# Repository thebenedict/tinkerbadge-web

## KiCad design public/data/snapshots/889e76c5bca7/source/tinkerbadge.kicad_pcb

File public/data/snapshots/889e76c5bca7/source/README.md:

# Tinker Badge hardware

Open **tinkerbadge.kicad_pro** in KiCad 10. The root schematic links to power, processor, display, lighting and peripheral sheets.

- [Specification](docs/spec.md)
- [Current schematic decisions and remaining gates](docs/design/implementation_status.md)
- [Design review, 10 November 2026](docs/design/design_review_2026-11-10.md)
- [Independent review, 11 November 2026](docs/review/design_review_2026-11-11.md) and [the response with the revision 0.3 fixes](docs/review/response_2026-11-11.md)
- [JLCPCB release package and order settings](docs/design/jlcpcb_release.md); order files in `production/jlcpcb/`
- [Reviewed physical-pin assignments](docs/pinouts.md)
- [Verification results](docs/design/verification.md)
- [Enclosure CAD, assembly and fit checks](mechanical/enclosure/README.md); STEP, STL and panel DXF files in `mechanical/enclosure/exports/`
- [Planning BOM and source history](docs/AI_Tinkerers_Badge_Design_BOM_Draft_2026-11-09.md)

The first prototype uses a single nominal 3.3 V rail for logic and the eight RGB LEDs. Regulator tolerance can fall below the LED datasheet minimum, so startup, low-battery, radio and full-white load-step tests are required.

PCB 0.4 retains Qwiic and exposes three GPIOs, serial, I²C and switched 3.3 V on [J503](docs/design/expansion_header.md). The board is fully routed. The A3 front plate provides access to the ten unpopulated holes.

This is a development design. The battery is a two-wire protected pouch cell on a rear JST PH header; charging is enabled at about 270 mA with on-board thermistors. The [review response](docs/review/response_2026-11-11.md) lists what changed in board revision 0.3 and what still needs hardware in hand, starting with a dry-fit of the display flex.

## Repeat the electrical check

Export the complete root schematic netlist using KiCad CLI or the installed Konnect MCP, then run:

```
python3 tools/check_schematic_contracts.py path/to/export.net --output path/to/endpoint-result.json
python3 tools/check_schematic_properties.py path/to/export.net --output path/to/property-result.json
python3 tools/test_contract_checker.py
python3 tools/test_property_checker.py
python3 tools/test_alps_buttons.py
```

The checker compares every physical pin and intentional NC with the separately maintained reviewed block contracts. The separate property checker covers explicitly declared values, part numbers, ratings, population and library associations. Run root ERC and inspect fresh sheet renders as well. Current outputs are in `exports/`, with a six-page PDF and a pinned verification manifest. The one-time capture scripts are not idempotent rebuild commands; rerunning them blindly can duplicate objects. Initial electrical capture used Konnect MCP. The user-approved [outlined-block revision](docs/design/outlined_blocks_review.md) uses bounded native edits, independent visual review and complete before/after exported-netlist comparison.

## Licensing

- Original hardware and mechanical designs: **CERN-OHL-P-2.0**.
- Original software, tools and firmware: **Apache-2.0**.
- Original documentation and artwork: **CC-BY-4.0**.

See [the licensing map](LICENSE.md) and [full license texts](LICENSES/README.md). Generated exports retain their source licenses. [Third-party notices](docs/THIRD_PARTY_NOTICES.md) cover KiCad libraries and manufacturer material.

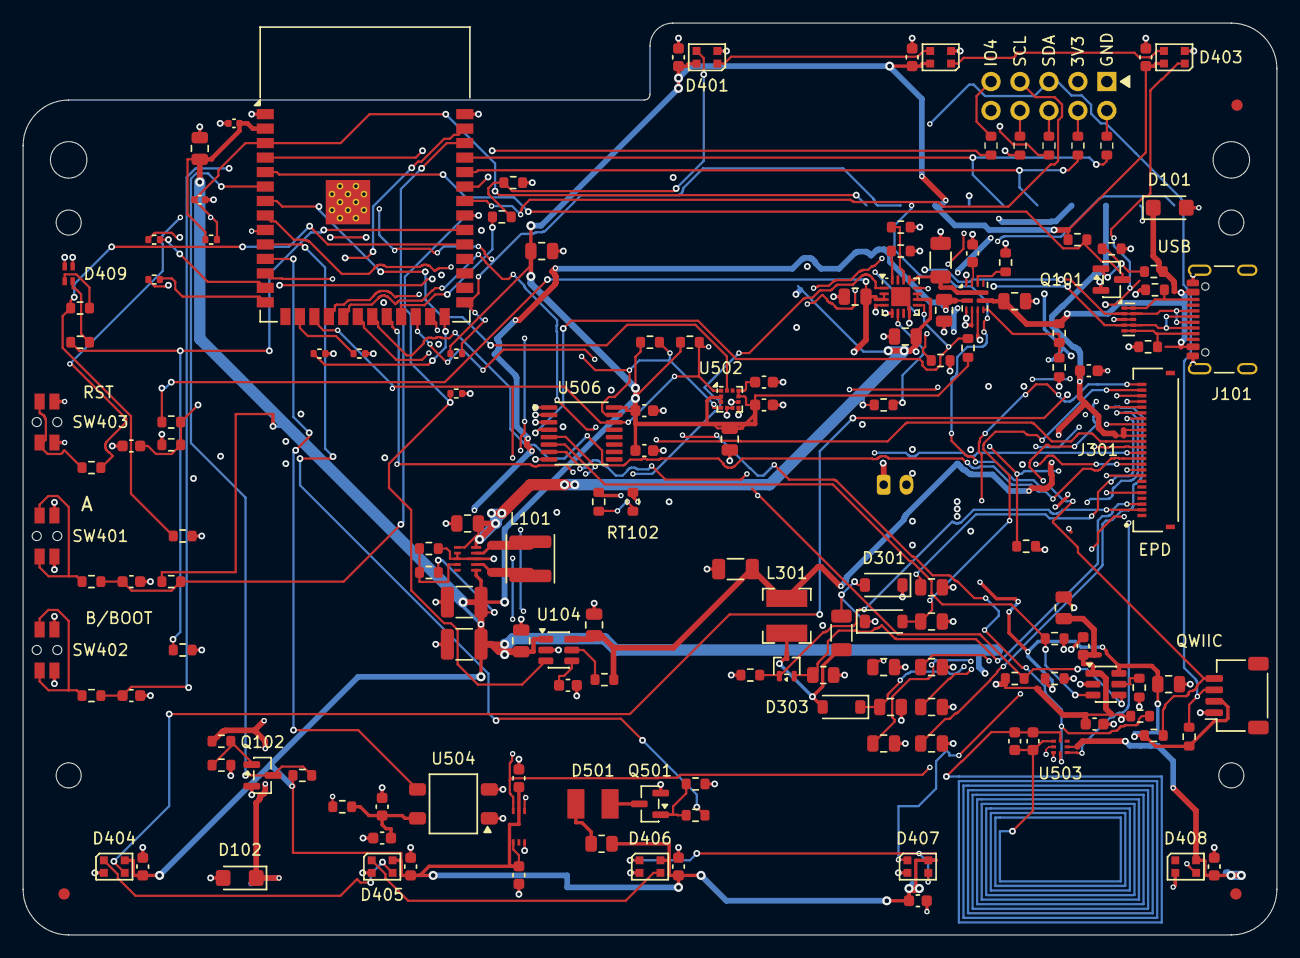
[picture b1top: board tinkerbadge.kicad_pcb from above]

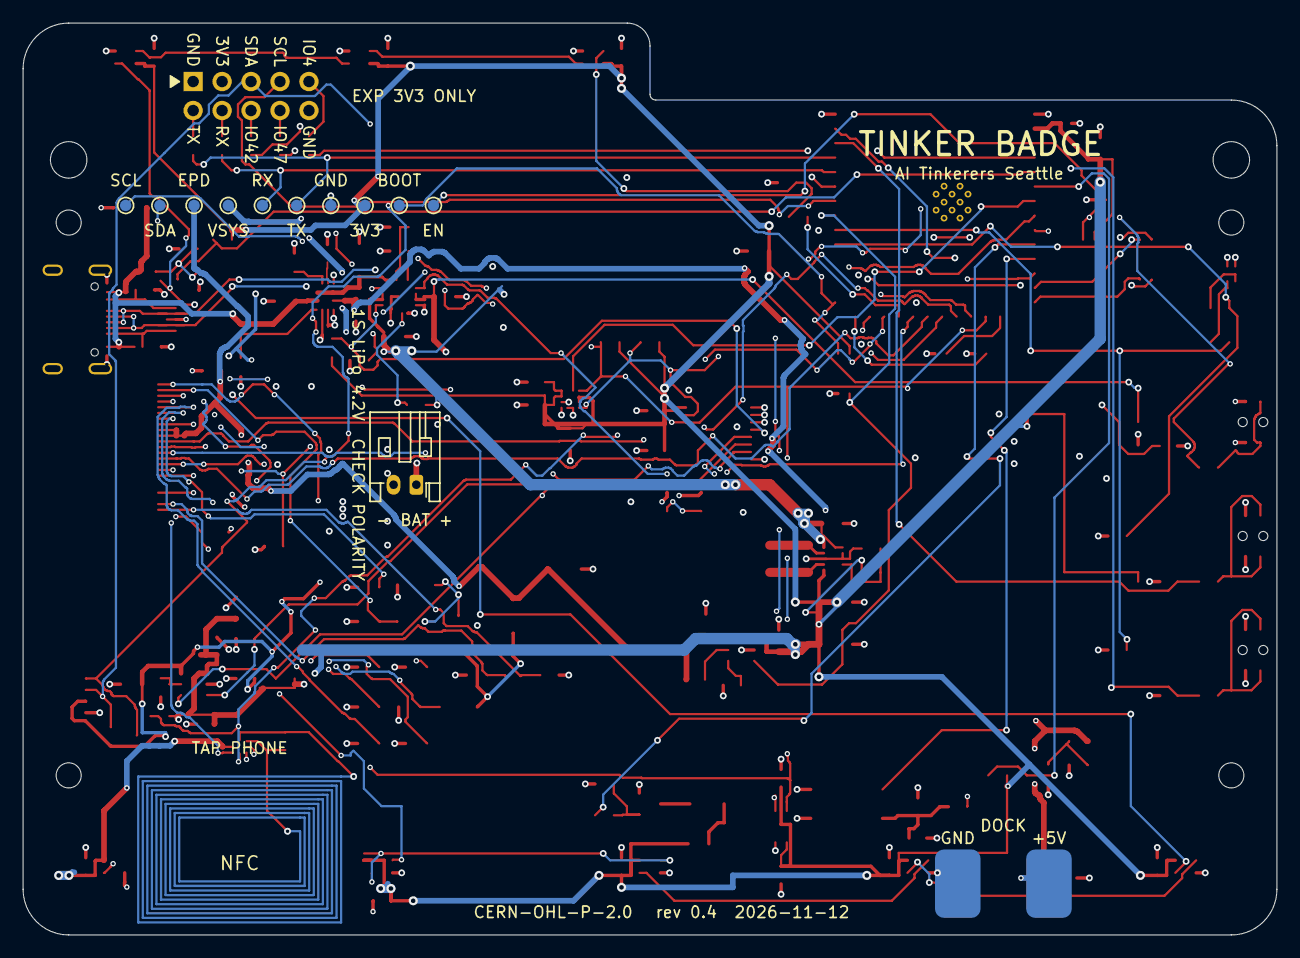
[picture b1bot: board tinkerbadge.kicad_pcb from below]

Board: 4 copper layers, 110.0 x 80.0 mm, 178 parts (14 on the bottom side), 102 nets.

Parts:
AE501: NFC PCB coil; NFC_Coil_Rear_18x13
C101, C102: 1uF 25V X7R; C_0805_2012Metric
C103: 4.7uF 25V X7R; C_1206_3216Metric
C104: 100nF 16V X7R; C_0603_1608Metric
C105, C106, C107: 10uF 10V X7R; C_0805_2012Metric
C108, C109: 22uF 10V X7R; C_1210_3225Metric
C112: 1uF 6.3V X7R; C_0805_2012Metric
C113: 1nF 16V C0G; C_0603_1608Metric
C114: 10uF 6.3V X7R; C_0805_2012Metric
C116: 100nF 6.3V X7R; C_0603_1608Metric
C201: 22uF 10V X5R; C_0805_2012Metric
C202: 100nF 16V X7R; C_0402_1005Metric
C203: 1uF 10V X7R; C_0402_1005Metric
C301, C302: 4.7u / 50V; C_1206_3216Metric
C303, C401, C402, C403, C404, C405, C406, C407, C408, C411, C412, C501, C502, C503, C504, C506, C510, C514: 100n / 10V; C_0603_1608Metric
C304: 1u / 10V; C_0805_2012Metric
C305, C311: 1u / 25V; C_0805_2012Metric
C306, C307, C308, C309, C310: 1u / 50V; C_0805_2012Metric
C409: 22u / 10V; C_0805_2012Metric
C505, C512, C513: 10u / 10V; C_0805_2012Metric
C507: 27p C0G (tune); C_0603_1608Metric
C508: TUNE / DNP; C_0603_1608Metric
C509: 4.7u / 10V; C_0603_1608Metric
C511, C515: 1u / 10V; C_0603_1608Metric
D101, D102: SMF6.0A
D301, D302, D303: MBR0530T1G; D_SOD-123
D401, D402, D403, D404, D405, D406, D407, D408: WS2812C-2020-V6; WS2812C-2020-V6_Reviewed
D409: HSMF-C165
D501: IR67-21C/TR8; IR67-21C_TR8
FID1, FID2, FID3: Fiducial; Fiducial_1mm_Mask2mm
H1, H2, H3, H4: PROVISIONAL; MountingHole_2.2mm_M2
H5, H6: REVIEW ENVELOPE ONLY; Review_Cord_Hole_3p2
J101: USB4105-GF-A; USB4105-GF-A_ProjectShells
J102: LiPo JST-PH; JST_PH_S2B-PH-K_1x02_P2.00mm_Horizontal
J103: Dock 5V pads; Dock_Pads_2x_4x6mm
J301: ED037TC1_FPC; Hirose_FH34SRJ-24S-0.5SH_PanelOrder
J501: SM04B-SRSS-TB(LF)(SN); JST_SH_SM04B_ProjectTabs
J503: 2x05 2.54 mm, not fitted; Expansion_Header_2x05_P2.54mm
L101: 0.47uH; L_Changjiang_FNR4020S
L301: 68uH; L_Bourns-SRN4018
MECH_BATTERY: REVIEW ONLY; Review_Battery_Allowance
MECH_PANEL: REVIEW ENVELOPE ONLY; Review_Panel_Raised_4p5
Q101, Q102, Q501: AO3400A; SOT-23
Q301: Si1308EDL-T1-GE3; SOT-323_SC-70
R101, R102: 5.1k 1%; R_0603_1608Metric
R107: 30k 1%; R_0603_1608Metric
R108, R118: 10k 1%; R_0603_1608Metric
R109: 82k 1%; R_0603_1608Metric
R111, R116, R121, R123, R124, R126: 100k 1%; R_0603_1608Metric
R112: 4.7k 1%; R_0603_1608Metric
R113: 3.3k 1%; R_0603_1608Metric
R114: 47k 1%; R_0603_1608Metric
R117: 56k 1%; R_0603_1608Metric
R119: 1k 1%; R_0603_1608Metric
R122, R125: 470k 1%; R_0603_1608Metric
R127, R128: 1M 1%; R_0603_1608Metric
R201, R202, R203, R204: 10k 1%; R_0402_1005Metric
R205, R206: 22R 1%; R_0402_1005Metric
R207: 100k 1%; R_0402_1005Metric
R301: 0.47 / 0.25W; R_0805_2012Metric
R302, R503: 10k; R_0603_1608Metric
R308, R402, R405, R406, R412, R506, R509, R510, R511: 100k; R_0603_1608Metric
R401, R411, R413, R415, R518, R519, R520, R521, R522: 330; R_0603_1608Metric
R403, R404: 2.2k; R_0603_1608Metric
R501, R502, R512, R513: 4.7k; R_0603_1608Metric
R504: 100; R_0805_2012Metric
R505, R507: 100; R_0603_1608Metric
R508: 200k; R_0603_1608Metric
RT101: 10k NTC B3950 1%; R_0603_1608Metric
RT102: 100k NTC B3950 1%; R_0603_1608Metric
SW401, SW402, SW403: SKSCLBE010
TP101: VSYS; TestPoint_Pad_D1.0mm
TP201: MCU_EN; TestPoint_Pad_D1.0mm
TP202: BOOT / BTN_B; TestPoint_Pad_D1.0mm
TP203: +3V3; TestPoint_Pad_D1.0mm
TP204: GND; TestPoint_Pad_D1.0mm
TP205: UART_TX; TestPoint_Pad_D1.0mm
TP206: UART_RX; TestPoint_Pad_D1.0mm
TP301: +3V3_EPD; TestPoint_Pad_D1.0mm
TP501: I2C_SDA; TestPoint_Pad_D1.0mm
TP502: I2C_SCL; TestPoint_Pad_D1.0mm
U101: TPS2121RUXR; TPS2121RUXR_Reviewed
U102: BQ24074RGTR; BQ24074RGTR_Reviewed
U103: TPS63802DLAR; TPS63802_DLA0010A_Reviewed
U104: TPS22918DBVR; SOT-23-6
U105: TPD4E05U06DQAR; USON-10_2.5x1.0mm_P0.5mm
U201: ESP32-S3-WROOM-1-N16R8; ESP32-S3-WROOM-1
U501: BH1730FVC; BH1730FVC_WSOF6
U502: LIS2DW12TR; LGA-12_2x2mm_P0.5mm
U503: NT3H2111W0FHKH; NT3H2111W0FHKH_XQFN8
U504: IRM-H638T/TR2; IRM-H638T_Reviewed
U505: TPS2553DBVR; SOT-23-6
U506: TCA9534PWR; TSSOP-16_4.4x5mm_P0.65mm

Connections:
+3V3: C108.1, C109.1, C112.1, C201.1, C202.1, C401.1, C402.1, C403.1, C404.1, C405.1, C406.1, C407.1, C408.1, C409.1, C501.1, C502.1, C503.1, C504.1, C505.1, C506.1, C511.1, C512.1, C514.1, C515.1, D401.4, D402.4, D403.4, D404.4, D405.4, D406.4, D407.4, D408.4, R116.1, R117.1, R123.1, R126.1, R201.1, R202.1, R412.1, R501.1, R502.1, R503.1, R504.1, R510.1, TP203.1, U103.6, U104.1, U201.2, U501.1, U501.5, U502.2, U502.3, U502.9, U502.10, U503.6, U505.1, U506.16
+3V3_EPD: C114.1, C301.1, C303.1, J301.15, J301.16, L301.1, R119.1, TP301.1, U104.6
/01 POWER + CHARGING/BATT_NTC: RT101.1, RT102.1, U102.1
/01 POWER + CHARGING/CHARGER_EN1: R111.2, U102.6
/01 POWER + CHARGING/CHARGER_ILIM: R112.1, U102.12
/01 POWER + CHARGING/CHARGER_ISET: R113.1, U102.16
/01 POWER + CHARGING/CHARGER_TMR: R114.1, U102.14
/01 POWER + CHARGING/DOCK_PRESENT_GATE: Q102.1, R124.2, R125.1
/01 POWER + CHARGING/EPD_CT: C113.1, U104.4
/01 POWER + CHARGING/EPD_QOD: R119.2, U104.5
/01 POWER + CHARGING/MUX_ILM: R109.1, U101.10
/01 POWER + CHARGING/MUX_PRIORITY_USB: R107.2, R108.1, U101.6
/01 POWER + CHARGING/MUX_SS: C104.1, U101.11
/01 POWER + CHARGING/PRIMARY_FB: R117.2, R118.1, U103.4
/01 POWER + CHARGING/PRIMARY_L1: L101.1, U103.9
/01 POWER + CHARGING/PRIMARY_L2: L101.2, U103.7
/01 POWER + CHARGING/USB_CC1: J101.A5, R101.1, U105.5, U105.6
/01 POWER + CHARGING/USB_CC2: J101.B5, R102.1, U105.1, U105.10
/01 POWER + CHARGING/USB_PRESENT_GATE: Q101.1, R121.2, R122.1
/01 POWER + CHARGING/VBAT_PROTECTED: C106.1, J102.1, R127.1, U102.2, U102.3
/01 POWER + CHARGING/VEXT_5V: C103.1, U101.1, U101.8, U102.13
/01 POWER + CHARGING/VSYS: C105.1, C107.1, R111.1, TP101.1, U102.10, U102.11, U103.1, U103.10
/02 PROCESSOR + RECOVERY/MCU_EN: C203.1, R201.2, R415.2, TP201.1, U201.3
/02 PROCESSOR + RECOVERY/MCU_EN_SW: R415.1, SW403.1, SW403.2
/02 PROCESSOR + RECOVERY/MCU_USB_DM: R205.2, U201.13
/02 PROCESSOR + RECOVERY/MCU_USB_DP: R206.2, U201.14
/02 PROCESSOR + RECOVERY/STRAP45: R203.1, U201.26
/02 PROCESSOR + RECOVERY/STRAP46: R204.1, U201.16
/03 E-PAPER DISPLAY/EPD_GDR: J301.2, Q301.1, R302.1
/03 E-PAPER DISPLAY/EPD_PUMP: C302.2, D301.2, D302.1
/03 E-PAPER DISPLAY/EPD_RESE: J301.3, Q301.2, R301.1
/03 E-PAPER DISPLAY/EPD_SW: C302.1, D303.2, L301.2, Q301.3
/03 E-PAPER DISPLAY/EPD_VCOM: C310.1, J301.24
/03 E-PAPER DISPLAY/EPD_VDD_1V8: C304.1, J301.18
/03 E-PAPER DISPLAY/EPD_VGH: C307.1, D303.1, J301.21
/03 E-PAPER DISPLAY/EPD_VGL: C309.1, D302.2, J301.23
/03 E-PAPER DISPLAY/EPD_VPP: C305.1, J301.19
/03 E-PAPER DISPLAY/EPD_VSH1: C306.1, J301.20
/03 E-PAPER DISPLAY/EPD_VSH2: C311.1, J301.5
/03 E-PAPER DISPLAY/EPD_VSL: C308.1, J301.22
/04 LIGHTING + BUTTONS/BTN_A_SW_N: R411.1, SW401.1, SW401.2
/04 LIGHTING + BUTTONS/BTN_B_SW_N: R413.1, SW402.1, SW402.2
/04 LIGHTING + BUTTONS/PWR_GREEN_A: D409.1, R403.2
/04 LIGHTING + BUTTONS/PWR_RED_A: D409.2, R404.2
/04 LIGHTING + BUTTONS/RGB_DIN: D401.3, R401.2, R402.1
/04 LIGHTING + BUTTONS/RGB_LINK_1: D401.1, D402.3
/04 LIGHTING + BUTTONS/RGB_LINK_2: D402.1, D403.3
/04 LIGHTING + BUTTONS/RGB_LINK_3: D403.1, D404.3
/04 LIGHTING + BUTTONS/RGB_LINK_4: D404.1, D405.3
/04 LIGHTING + BUTTONS/RGB_LINK_5: D405.1, D406.3
/04 LIGHTING + BUTTONS/RGB_LINK_6: D406.1, D407.3
/04 LIGHTING + BUTTONS/RGB_LINK_7: D407.1, D408.3
/05 SENSORS + EXPANSION/ACC_3V3: C513.1, J501.2, J503.3, R511.1, R512.1, R513.1, U505.6
/05 SENSORS + EXPANSION/ACC_EN: R509.1, U505.3, U506.6
/05 SENSORS + EXPANSION/ACC_FAULT_N: R510.2, U505.4, U506.7
/05 SENSORS + EXPANSION/ACC_ILIM: R508.1, U505.5
/05 SENSORS + EXPANSION/HDR_IO4: J503.9, R522.2
/05 SENSORS + EXPANSION/HDR_IO42: J503.6, R520.2
/05 SENSORS + EXPANSION/HDR_IO47: J503.8, R521.2
/05 SENSORS + EXPANSION/HDR_RX: J503.4, R519.2
/05 SENSORS + EXPANSION/HDR_TX: J503.2, R518.2
/05 SENSORS + EXPANSION/IR_GATE: Q501.1, R505.2, R506.1
/05 SENSORS + EXPANSION/IR_LED_A: D501.1, R504.2
/05 SENSORS + EXPANSION/IR_LED_K: D501.2, Q501.3
/05 SENSORS + EXPANSION/IR_RX_3V3: C509.1, C510.1, R507.2, U504.4
/05 SENSORS + EXPANSION/IR_RX_EN: R507.1, U506.5
/05 SENSORS + EXPANSION/NFC_LA: AE501.1, C507.1, C508.1, U503.1
/05 SENSORS + EXPANSION/NFC_LB: AE501.2, C507.2, C508.2, U503.8
BAT_ADC: C116.1, R127.2, R128.1, U201.39
BTN_A_N: C411.1, R411.2, R412.2, U201.38
BTN_B_N: C412.1, R202.2, R413.2, TP202.1, U201.27
CHARGER_CHG_N: R116.2, U102.9, U506.4
DOCK_5V: C102.1, D102.1, J103.1, R124.1, U101.2
DOCK_PRESENT_N: Q102.3, R126.2, U201.6
EPD_BUSY: J301.9, R308.1, U201.8
EPD_CS_N: J301.12, U201.18
EPD_DC: J301.11, U201.21
EPD_EN: R207.1, U104.3, U201.33
EPD_MOSI: J301.14, U201.19
EPD_RST_N: J301.10, U201.22
EPD_SCK: J301.13, U201.20
EXP_IO4: R522.1, U201.4
EXP_IO42: R520.1, U201.35
EXP_IO47: R521.1, U201.24
EXT_SCL: J501.4, J503.7, R513.2, U201.34
EXT_SDA: J501.3, J503.5, R512.2, U201.9
GND: C101.2, C102.2, C103.2, C104.2, C105.2, C106.2, C107.2, C108.2, C109.2, C112.2, C113.2, C114.2, C116.2, C201.2, C202.2, C203.2, C301.2, C303.2, C304.2, C305.2, C306.2, C307.2, C308.2, C309.2, C310.2, C311.2, C401.2, C402.2, C403.2, C404.2, C405.2, C406.2, C407.2, C408.2, C409.2, C411.2, C412.2, C501.2, C502.2, C503.2, C504.2, C505.2, C506.2, C509.2, C510.2, C511.2, C512.2, C513.2, C514.2, C515.2, D101.2, D102.2, D301.1, D401.2, D402.2, D403.2, D404.2, D405.2, D406.2, D407.2, D408.2, D409.3, D409.4, J101.A1, J101.A12, J101.B1, J101.B12, J101.SH, J102.2, J103.2, J301.8, J301.17, J501.1, J503.1, J503.10, Q101.2, Q102.2, Q501.2, R101.2, R102.2, R108.2, R109.2, R112.2, R113.2, R114.2, R118.2, R122.2, R125.2, R128.2, R203.2, R204.2, R207.2, R301.2, R302.2, R308.2, R402.2, R405.2, R406.2, R506.2, R508.2, R509.2, R511.2, RT101.2, RT102.2, SW401.3, SW401.4, SW402.3, SW402.4, SW403.3, SW403.4, TP204.1, U101.3, U101.4, U101.5, U101.12, U102.4, U102.5, U102.8, U102.17, U103.2, U103.3, U103.8, U104.2, U105.3, U105.8, U201.1, U201.40, U201.41, U501.3, U502.5, U502.6, U502.7, U502.8, U503.2, U504.1, U504.2, U505.2, U506.1, U506.2, U506.3, U506.8
I2C_SCL: R502.2, TP502.1, U201.17, U501.6, U502.1, U503.3, U506.14
I2C_SDA: R501.2, TP501.1, U201.12, U501.4, U502.4, U503.5, U506.15
IR_RX_N: U201.11, U504.3
IR_TX: R505.1, U201.10
MOTION_INT1: U201.7, U502.12
NFC_FD_N: R503.2, U201.25, U503.4
PWR_LED_G: R403.1, R405.1, U201.31
PWR_LED_R: R404.1, R406.1, U201.32
RGB_DATA: R401.1, U201.23
UART_RX: R519.1, TP206.1, U201.36
UART_TX: R518.1, TP205.1, U201.37
USB_DM: J101.A7, J101.B7, R205.1, U105.4, U105.7
USB_DP: J101.A6, J101.B6, R206.1, U105.2, U105.9
USB_PRESENT_N: Q101.3, R123.2, U201.5
USB_VBUS: C101.1, D101.1, J101.A4, J101.A9, J101.B4, J101.B9, R107.1, R121.1, U101.7

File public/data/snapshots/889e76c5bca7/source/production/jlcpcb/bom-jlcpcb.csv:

Comment,Designator,Footprint,LCSC Part #,Manufacturer Part,Qty
1uF 25V X7R,"C101,C102,C112,C304,C305,C306,C307,C308,C309,C310,C311",C_0805_2012Metric,C28323,CL21B105KBFNNNE,11
4.7uF 25V X7R,"C103,C301,C302",C_1206_3216Metric,C29823,1206B475K500NT,3
100nF 16V X7R,"C104,C116,C303,C401,C402,C403,C404,C405,C406,C407,C408,C411,C412,C501,C502,C503,C504,C506,C510,C514",C_0603_1608Metric,C14663,CC0603KRX7R9BB104,20
10uF 10V X7R,"C105,C106,C107,C114,C505,C512,C513",C_0805_2012Metric,C15850,CL21A106KAYNNNE,7
22uF 10V X7R,"C108,C109",C_1210_3225Metric,C309062,CL32B226KAJNNNE,2
1nF 16V C0G,C113,C_0603_1608Metric,C1588,CL10B102KB8NNNC,1
22uF 10V X5R,"C201,C409",C_0805_2012Metric,C45783,CL21A226MAQNNNE,2
100nF 16V X7R,C202,C_0402_1005Metric,C1525,CL05B104KO5NNNC,1
1uF 10V X7R,C203,C_0402_1005Metric,C52923,CL05A105KA5NQNC,1
27p C0G (tune),C507,C_0603_1608Metric,C107045,CC0603JRNPO9BN270,1
4.7u / 10V,C509,C_0603_1608Metric,C19666,CL10A475KO8NNNC,1
1u / 10V,"C511,C515",C_0603_1608Metric,C15849,CL10A105KB8NNNC,2
SMF6.0A,"D101,D102",SMF6.0A,C19077499,SMF6.0A,2
MBR0530T1G,"D301,D302,D303",D_SOD-123,C82046,MBR0530T1G,3
WS2812C-2020-V6,"D401,D402,D403,D404,D405,D406,D407,D408",WS2812C-2020-V6_Reviewed,C55109522,WS2812C-2020-V6,8
HSMF-C165,D409,HSMF-C165,C188726,HSMF-C165,1
IR67-21C/TR8,D501,IR67-21C_TR8,C60109,IR67-21C/TR8,1
USB4105-GF-A,J101,USB4105-GF-A_ProjectShells,C3020560,USB4105-GF-A,1
ED037TC1_FPC,J301,Hirose_FH34SRJ-24S-0.5SH_PanelOrder,C324726,FH34SRJ-24S-0.5SH(50),1
SM04B-SRSS-TB(LF)(SN),J501,JST_SH_SM04B_ProjectTabs,C160404,SM04B-SRSS-TB(LF)(SN),1
0.47uH,L101,L_Changjiang_FNR4020S,C98415,SWPA4020SR47NT,1
68uH,L301,L_Bourns-SRN4018,C2041717,SRN4018-680M,1
AO3400A,"Q101,Q102,Q501",SOT-23,C20917,AO3400A,3
Si1308EDL-T1-GE3,Q301,SOT-323_SC-70,C469327,SI1308EDL-T1-GE3,1
5.1k 1%,"R101,R102",R_0603_1608Metric,C23186,0603WAF5101T5E,2
30k 1%,R107,R_0603_1608Metric,C22984,0603WAF3002T5E,1
10k 1%,"R108,R118,R302,R503",R_0603_1608Metric,C25804,0603WAF1002T5E,4
82k 1%,R109,R_0603_1608Metric,C23254,0603WAF8202T5E,1
100k 1%,"R111,R116,R121,R123,R124,R126,R308,R402,R405,R406,R412,R506,R509,R510,R511",R_0603_1608Metric,C25803,0603WAF1003T5E,15
4.7k 1%,"R112,R501,R502,R512,R513",R_0603_1608Metric,C23162,0603WAF4701T5E,5
3.3k 1%,R113,R_0603_1608Metric,C22978,0603WAF3301T5E,1
47k 1%,R114,R_0603_1608Metric,C25819,0603WAF4702T5E,1
56k 1%,R117,R_0603_1608Metric,C23206,0603WAF5602T5E,1
1k 1%,R119,R_0603_1608Metric,C21190,0603WAF1001T5E,1
470k 1%,"R122,R125",R_0603_1608Metric,C23178,0603WAF4703T5E,2
1M 1%,"R127,R128",R_0603_1608Metric,C22935,0603WAF1004T5E,2
10k 1%,"R201,R202,R203,R204",R_0402_1005Metric,C25744,0402WGF1002TCE,4
22R 1%,"R205,R206",R_0402_1005Metric,C25092,0402WGF220JTCE,2
100k 1%,R207,R_0402_1005Metric,C25741,0402WGF1003TCE,1
0.47 / 0.25W,R301,R_0805_2012Metric,C382278,FBF05FT-R470-00L,1
330,"R401,R411,R413,R415,R518,R519,R520,R521,R522",R_0603_1608Metric,C23138,0603WAF3300T5E,9
2.2k,"R403,R404",R_0603_1608Metric,C4190,0603WAF2201T5E,2
100,R504,R_0805_2012Metric,C17408,0805W8F1000T5E,1
100,"R505,R507",R_0603_1608Metric,C22775,0603WAF1000T5E,2
200k,R508,R_0603_1608Metric,C25811,0603WAF2003T5E,1
10k NTC B3950 1%,RT101,R_0603_1608Metric,C2892547,KNTC0603/10KF3950,1
100k NTC B3950 1%,RT102,R_0603_1608Metric,C2892545,KNTC0603/100KF3950,1
SKSCLBE010,"SW401,SW402,SW403",SKSCLBE010,C115361,SKSCLBE010,3
TPS2121RUXR,U101,TPS2121RUXR_Reviewed,C485916,TPS2121RUXR,1
BQ24074RGTR,U102,BQ24074RGTR_Reviewed,C54313,BQ24074RGTR,1
TPS63802DLAR,U103,TPS63802_DLA0010A_Reviewed,C2845237,TPS63802DLAR,1
TPS22918DBVR,U104,SOT-23-6,C131941,TPS22918DBVR,1
TPD4E05U06DQAR,U105,USON-10_2.5x1.0mm_P0.5mm,C138714,TPD4E05U06DQAR,1
ESP32-S3-WROOM-1-N16R8,U201,ESP32-S3-WROOM-1,C2913202,ESP32-S3-WROOM-1-N16R8,1
BH1730FVC,U501,BH1730FVC_WSOF6,C79616,BH1730FVC,1
LIS2DW12TR,U502,LGA-12_2x2mm_P0.5mm,C189624,LIS2DW12TR,1
NT3H2111W0FHKH,U503,NT3H2111W0FHKH_XQFN8,C710403,NT3H2111W0FHKH,1
IRM-H638T/TR2,U504,IRM-H638T_Reviewed,C91447,IRM-H638T/TR2,1
TPS2553DBVR,U505,SOT-23-6,C55266,TPS2553DBVR,1
TCA9534PWR,U506,TSSOP-16_4.4x5mm_P0.65mm,C783615,TCA9534PWR,1
